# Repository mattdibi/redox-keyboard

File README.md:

<h3 align="center">The Redox project repository</h3>

<div align="center">

</div>

---

The Redox project is an open-source, [QMK (Quantum Mechanical Keyboard Firmware)](https://github.com/qmk/qmk_firmware) powered, ergonomic split mechanical keyboard. This repository will be used to share information about the project and instruction on how to use and assemble the Redox keyboard.

**Designer's bio**: [Mattia Dal Ben (aka u/TiaMaT102)](mailto:matthewdibi@gmail.com) obtained a master's degree in Electrical Engineering with a specialization in Computer Science at the University of Udine. Currently works as a Software Engineer in R&D department for a big IoT and Embedded Computers company. Mechanical keyboard enthusiast and maker, the Redox keyboard is the result of all of his passions.

## Rationale

The Redox is a keyboard project designed with ergonomics in mind. It uses Cherry MX style mechanical switches laid out in a 7x5 columnar stagger layout with components that can easily be sourced.

The design was heavily inspired by the [Ergodox keyboard](https://www.ergodox.io/), and its main goal is to reduce the size without sacrificing too many keys, hence the name **Re**duced Ergo**dox**.

As an Ergodox user I couldn't ignore the few flaws of the original design and in a moment of arrogance I tried to fix them, thus the Redox features:
- Easier to reach thumb cluster.
- Additional easy-to-reach rotated 1.25u thumb key.
- Reduced size.
- Reduced costs (the Redox uses Arduino Pro Micro instead of the Teensy 2.0).
- Either half can be plugged in to the PC since each half can act as the master.
- Either half can work as a standalone keyboard to be used as a macropad/gaming keyboard.
- RGB backlighting support.
- 3D-printer friendly case.
- Wireless [see section below](#wireless-implementations)
- [VIA](https://caniusevia.com/) compatible (thanks to [Harshit Goel](https://github.com/harshitgoel96))
- [ZMK firmware](https://zmk.dev/) compatible (thanks to [toddmok](https://github.com/toddmok))
- [KMK firmware](http://kmkfw.io/) compatible

## Related Projects

- [**Redox handwire**](https://www.thingiverse.com/thing:2704567): The first incarnation of the Redox keyboard. It consists of a 3D-printed case and a handwired matrix.
  - [Tilted Redox case](https://www.thingiverse.com/thing:2767216): tilted case for the Redox prototype by jschloer.
    - [Tilted redox case pro micro](https://www.printables.com/model/382413-tilted-redox-case-for-micro-and-usbc): Remix of the tilted case to support pro micro and usb c instead of TRRS. 

  - [couscous-kbd](https://gitlab.com/cschalkwijk/couscous-kbd): Redox-inspired parametric OpenSCAD keyboard design.
  - [Redox tenting kit](https://www.thingiverse.com/make:484843): modified base to support tenting, mini-USB for the interconnect, and a hole for microswitch for reset needed when uploading new firmware by [Lenbok](https://github.com/Lenbok).
  - [Iris-inspired Redox case](https://github.com/Lenbok/scad-redox-case): a case inspired both by the Redox rev1.0 and the Iris designed with OpenSCAD by [Lenbok](https://github.com/Lenbok).
  - [Redodactyl keyboard](https://www.reddit.com/r/MechanicalKeyboards/comments/9j5pw5/enter_the_redodactyl_first_build/): handwired 3D printed Dactyl-inspired Redox variant by u/darknao.
- [**Redox Manuform**](https://www.thingiverse.com/thing:3503380): full rework of the Redox case inspired by the Dactyl Manuform. Designed by [Fosk\_LL](https://www.thingiverse.com/Fosk_LL/about).
- [**Redox rev1.0**](https://github.com/mattdibi/redox-keyboard/tree/master/redox): the Redox rev 1.0 is the first commercially available version of the Redox keyboard.
	- Rev1.0 PCBs: available at [Falbatech's store](https://falbatech.click/products/REDOX-PCB-Electrical-Boards-Set-of-2-p613836203)
    - Firmware sources:
        - [QMK firmware for Redox](https://github.com/mattdibi/qmk_firmware/tree/master/keyboards/redox)
        - [KMK firmware for Redox](https://github.com/KMKfw/kmk_firmware/tree/master/boards/redox)
	- 3D-printable cases:
        - [3D printable case](https://www.thingiverse.com/thing:2886662), freely available.
        - [Redox keyboard case (high profile)](https://www.thingiverse.com/thing:3825752), by [Michele Ferri](https://www.thingiverse.com/sako83/about).
        - [Travel-friendly Redox Keyboard case](https://www.thingiverse.com/thing:3607303), by [Fosk\_LL](https://www.thingiverse.com/Fosk_LL/about).
        - [Redox Neodox case](https://github.com/Pastitas/Redox-neodox-Case), by [Pastitas](https://github.com/Pastitas)
        - [Redox big battery](https://github.com/marco-silvestri/redox-big-battery), by [Marco Silvestri](https://github.com/marco-silvestri).
	- Commercially available cases:
		- [Falbatech's bamboo cases with tilt kit](https://falbatech.click/products/REDOX-Standard-LIFT-Bamboo-Wood-Case-with-oil-finish-p613843480)
		- [Falbatech's fullhand bamboo cases](https://falbatech.click/products/search?keyword=redox%20fullhand%20bamboo)
- [**Redox rev1.0W**](https://github.com/mattdibi/redox-keyboard/tree/master/redox-w): the Redox rev 1.0W is the wireless version of the Redox keyboard.
    - Rev1.0W PCBs: gerbers available in [this repo](https://github.com/mattdibi/redox-keyboard/tree/master/redox-w/rev1.0W).
    - Falbatech's Rev1.0W Hot-swap PCBs: available at [Falbatech's store](https://falbatech.click/products/REDOX-Wireless-PCB-Electrical-Boards-Set-of-2-receiver-PCB-p613839986) (Incompatible with the 3D-printable cases down below)
    - Firmware sources:
        - [QMK firmware for Redox wireless](https://github.com/mattdibi/qmk_firmware/tree/master/keyboards/redox_w)
        - [Nordic MCUs firmware for Redox wireless](https://github.com/mattdibi/redox-w-firmware)
	- 3D-printable cases:
        - [3D printed case](https://github.com/mattdibi/redox-keyboard/tree/master/redox-w/case), freely available.
        - [Redox Neodox case](https://github.com/Pastitas/Redox-neodox-Case), by [Pastitas](https://github.com/Pastitas)
    - Commercially available cases (only compatible with the Falbatech's store PCBs):
        - [Falbatech's bamboo cases with tilt kit](https://falbatech.click/products/REDOX-Wireless-Standard-LIFT-Bamboo-Wood-Case-with-oil-finish-ver-1-p613842405)
		- [Falbatech's fullhand bamboo cases](https://falbatech.click/products/search?keyword=redox%20wireless%20bamboo%20fullhand)
- [**Redox rev2.0WHS**](https://github.com/mattdibi/redox-keyboard/tree/master/redox-w): the Redox rev 2.0WHS is the wireless hot-swappable version of the Redox keyboard.
    - Rev2.0WHS PCBs: gerber files available [here](https://github.com/mattdibi/redox-keyboard/tree/master/redox-w/rev2.0WHS/pcb)
    - Firmware sources:
        - [QMK firmware for Redox wireless](https://github.com/mattdibi/qmk_firmware/tree/master/keyboards/redox_w)
        - [Nordic MCUs firmware for Redox wireless](https://github.com/mattdibi/redox-w-firmware)
	- 3D-printable case:
        - [3D printed case](https://github.com/mattdibi/redox-keyboard/tree/master/redox-w/rev2.0WHS/case), freely available.

## Wireless Implementations

The Redox keyboard uses three different wireless implementations, differentiated by firmware:
 - *QMK based*: Leveraging the [Gazel protocol](https://developer.nordicsemi.com/nRF5_SDK/nRF51_SDK_v5.x.x/doc/5.2.0/html/a00140.html). It needs its own PCB and a receiver dongle (see [Redox Wireless](https://github.com/mattdibi/redox-keyboard/tree/master/redox-w) for details) and needs three YJ-14015 MCUs + a Pro Micro compatible controller.
 - *ZMK based*: Leveraging the Bluetooth protocol. It is based on the [Redox wired PCB](https://github.com/mattdibi/redox-keyboard/tree/master/redox) and the [nice!nano](https://nicekeyboards.com/nice-nano/) controller.
 - *KMK based*: Adding [Bluetooth Split](http://kmkfw.io/docs/split_keyboards#bluetooth-split-aka-no-trrs-currently-in-testing) code to `boards/redox/main.py`. Combined with a [compatible](http://kmkfw.io/docs/Officially_Supported_Microcontrollers) wireless controller completes wireless configuration. Would advice adding [Bluetooth keycodes](http://kmkfw.io/docs/keycodes#bluetooth-keys) in keymap; `keyboard.keymap` element in `main.py`.

 The notable differences for the three implementations are as follows:
 - _Battery life_: QMK Redox Wireless uses two CR2032 coin cell batteries which last [approximately one year (YMMV)](https://github.com/mattdibi/redox-keyboard/tree/master/redox-w#battery-usage), while the nice!nano support LiPo rechargable batteries (you can choose the capacity you want but expect them to last for a [few weeks on a single charge](https://zmk.dev/power-profiler)).
 - _Flexibility_: The receiver dongle limits the flexibility of QMK Redox Wireless.
 - _Cost_: The 3x YJ-14015 + Pro Micro combo is cheaper than two wireless controllers required for ZMK and wireless KMK.
 - _Range_: Bluetooth implementations, of ZMK and KMK, should be more capable than what can be achieved with the QMK Redox Wireless (At this point in time, I lack the evidence to support these claims though).

## Physical Key Layout

### Keycaps

| Size  | Qty |                                     Notes                                    |
|-------|:---:|:----------------------------------------------------------------------------:|
| 1.5u  |   6 |                                                                              |
| 1.25u |  10 | You can get away with 8 if you use two 1u keycaps for the 1.25u rotated keys |
| 1u    |  54 |                                                                              |

> :information_source: On [pimpmykeyboard.com](https://pimpmykeyboard.com/sa-1976-keyset-two-shot/) site you can find a SA 1976 keyset kit specifically made for the Redox keyboard: the "Ergo Redox kit (12 keys)".

## Affiliations

In partnership with Falbatech you can now use the code "**mattdibi05**" on Falbatech's store for a 5% OFF special discount.

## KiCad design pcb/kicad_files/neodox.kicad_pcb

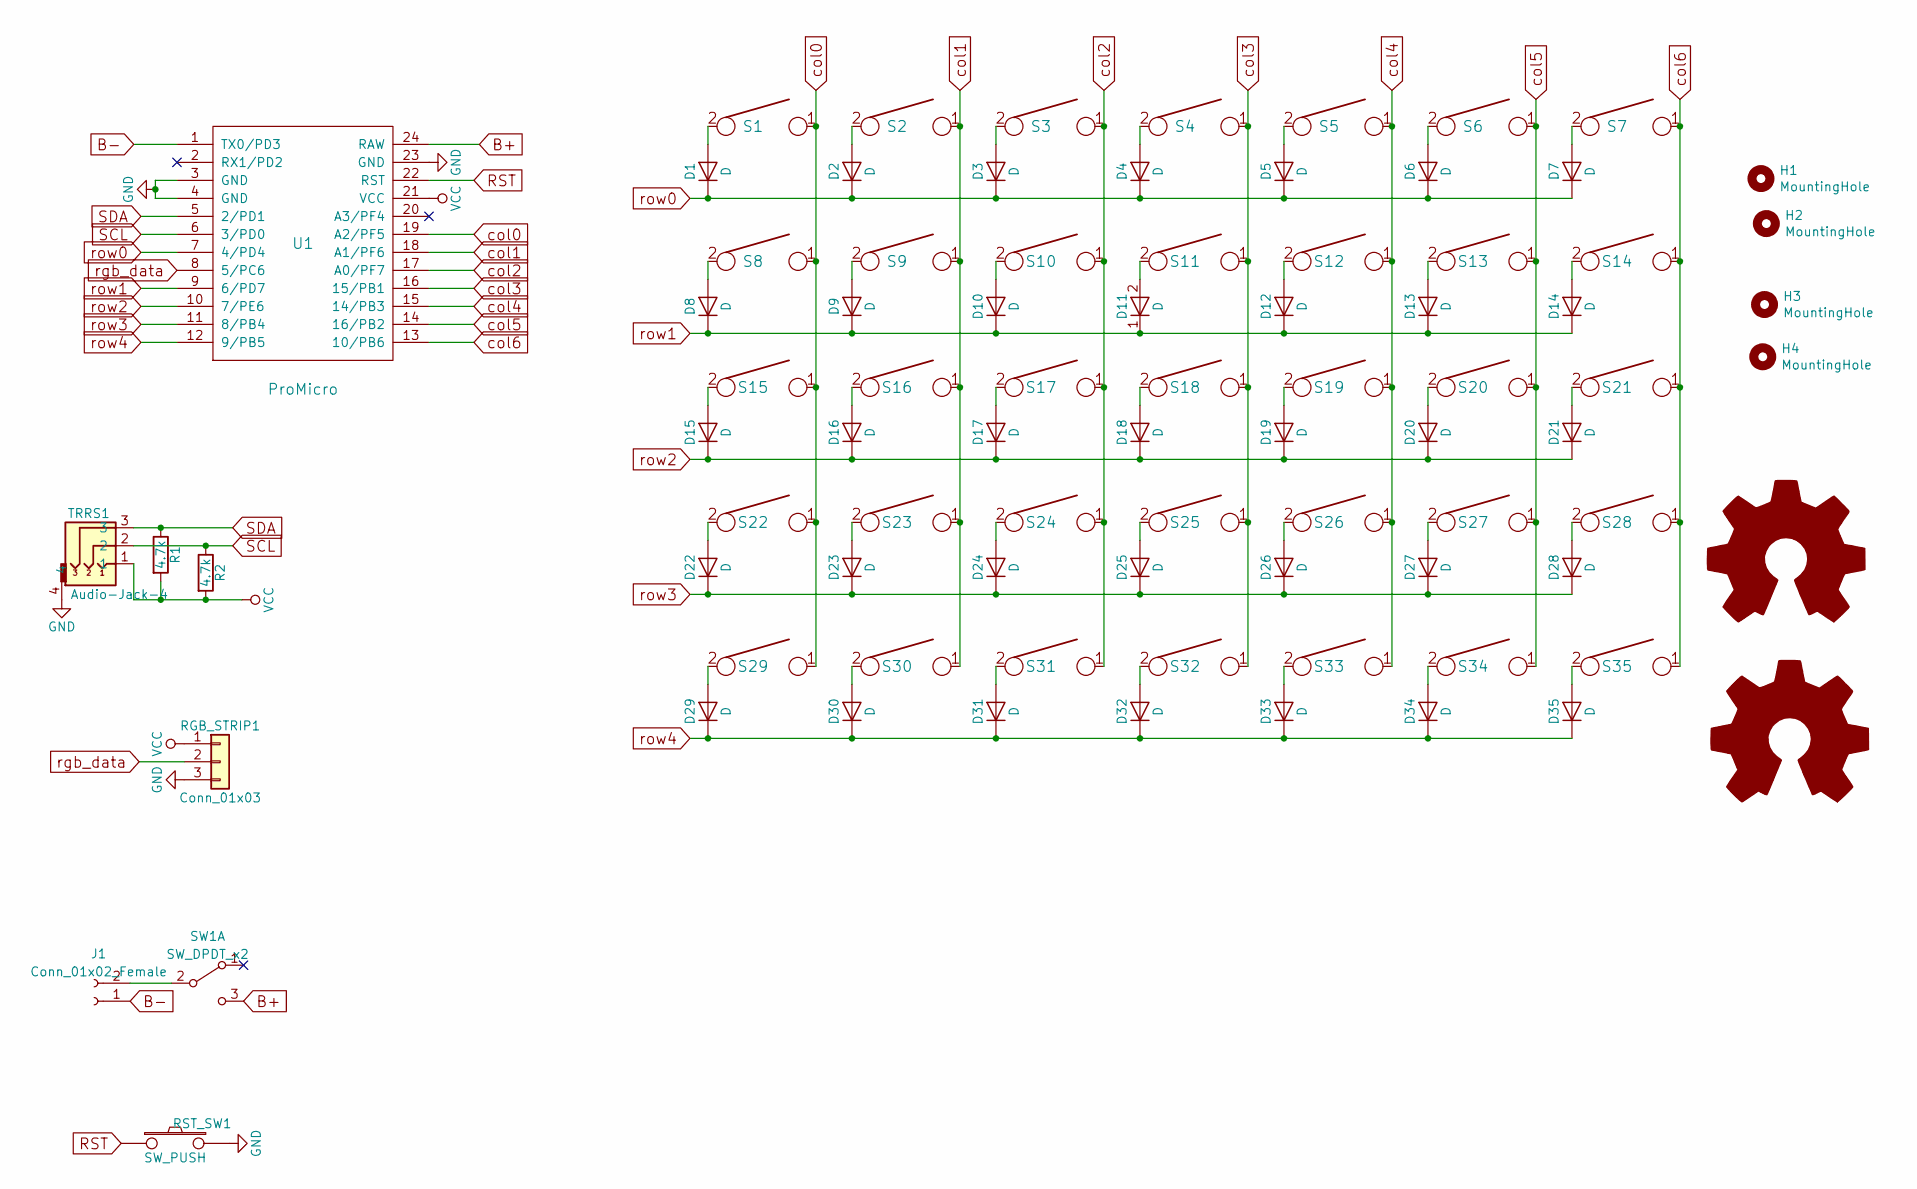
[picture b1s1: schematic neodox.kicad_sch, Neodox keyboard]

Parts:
D1, D2, D3, D4, D5, D6, D7, D8, D9, D10, D11, D12, D13, D14, D15, D16, D17, D18, D19, D20, D21, D22, D23, D24, D25, D26, D27, D28, D29, D30, D31, D32, D33, D34, D35: D; Diode-dual
H1, H2, H3, H4: MountingHole; MountingHole_3.2mm_M3
J1: Conn_01x02_Female; PinHeader_1x02_P1.27mm_Vertical
R1, R2: 4.7k; Resistor-Hybrid
RGB_STRIP1: Conn_01x03; PinHeader_1x03_P1.27mm_Vertical
RST_SW1: SW_PUSH; pushbutton_reversible
S1, S2, S3, S4, S5, S6, S7, S8, S9, S10, S11, S12, S13, S14, S15, S16, S17, S18, S19, S20, S21, S22, S23, S24, S25, S26, S27, S28, S29, S30, S31, S32, S33, S34, S35: KEYSW; Kailh_socket_MX_optional_reversible
SW1: SW_DPDT_x2; switch_reversible
TRRS1: Audio-Jack-4; PJ-320A
U1: ProMicro; ProMicro_unrouted

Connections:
B+: SW1.3 (C), U1.24 (RAW)
B-: J1.1, U1.1 (TX0/PD3)
GND: RGB_STRIP1.3, RST_SW1.2, TRRS1.4, U1.3 (GND), U1.4 (GND), U1.23 (GND)
unnamed: D1.2 (A), S1.2
unnamed: D2.2 (A), S2.2
unnamed: D3.2 (A), S3.2
unnamed: D4.2 (A), S4.2
unnamed: D5.2 (A), S5.2
unnamed: D6.2 (A), S6.2
unnamed: D7.2 (A), S7.2
unnamed: D8.2 (A), S8.2
unnamed: D9.2 (A), S9.2
unnamed: D10.2 (A), S10.2
unnamed: D11.2 (A), S11.2
unnamed: D12.2 (A), S12.2
unnamed: D13.2 (A), S13.2
unnamed: D14.2 (A), S14.2
unnamed: D15.2 (A), S15.2
unnamed: D16.2 (A), S16.2
unnamed: D17.2 (A), S17.2
unnamed: D18.2 (A), S18.2
unnamed: D19.2 (A), S19.2
unnamed: D20.2 (A), S20.2
unnamed: D21.2 (A), S21.2
unnamed: D22.2 (A), S22.2
unnamed: D23.2 (A), S23.2
unnamed: D24.2 (A), S24.2
unnamed: D25.2 (A), S25.2
unnamed: D26.2 (A), S26.2
unnamed: D27.2 (A), S27.2
unnamed: D28.2 (A), S28.2
unnamed: D29.2 (A), S29.2
unnamed: D30.2 (A), S30.2
unnamed: D31.2 (A), S31.2
unnamed: D32.2 (A), S32.2
unnamed: D33.2 (A), S33.2
unnamed: D34.2 (A), S34.2
unnamed: D35.2 (A), S35.2
unnamed: J1.2, SW1.2 (B)
RST: RST_SW1.1, U1.22 (RST)
SCL: R2.1, TRRS1.2, U1.6 (3/PD0)
SDA: R1.1, TRRS1.3, U1.5 (2/PD1)
VCC: R1.2, R2.2, RGB_STRIP1.1, TRRS1.1, U1.21 (VCC)
col0: S1.1, S8.1, S15.1, S22.1, S29.1, U1.19 (A2/PF5)
col1: S2.1, S9.1, S16.1, S23.1, S30.1, U1.18 (A1/PF6)
col2: S3.1, S10.1, S17.1, S24.1, S31.1, U1.17 (A0/PF7)
col3: S4.1, S11.1, S18.1, S25.1, S32.1, U1.16 (15/PB1)
col4: S5.1, S12.1, S19.1, S26.1, S33.1, U1.15 (14/PB3)
col5: S6.1, S13.1, S20.1, S27.1, S34.1, U1.14 (16/PB2)
col6: S7.1, S14.1, S21.1, S28.1, S35.1, U1.13 (10/PB6)
rgb_data: RGB_STRIP1.2, U1.8 (5/PC6)
row0: D1.1 (K), D2.1 (K), D3.1 (K), D4.1 (K), D5.1 (K), D6.1 (K), D7.1 (K), U1.7 (4/PD4)
row1: D8.1 (K), D9.1 (K), D10.1 (K), D11.1 (K), D12.1 (K), D13.1 (K), D14.1 (K), U1.9 (6/PD7)
row2: D15.1 (K), D16.1 (K), D17.1 (K), D18.1 (K), D19.1 (K), D20.1 (K), D21.1 (K), U1.10 (7/PE6)
row3: D22.1 (K), D23.1 (K), D24.1 (K), D25.1 (K), D26.1 (K), D27.1 (K), D28.1 (K), U1.11 (8/PB4)
row4: D29.1 (K), D30.1 (K), D31.1 (K), D32.1 (K), D33.1 (K), D34.1 (K), D35.1 (K), U1.12 (9/PB5)

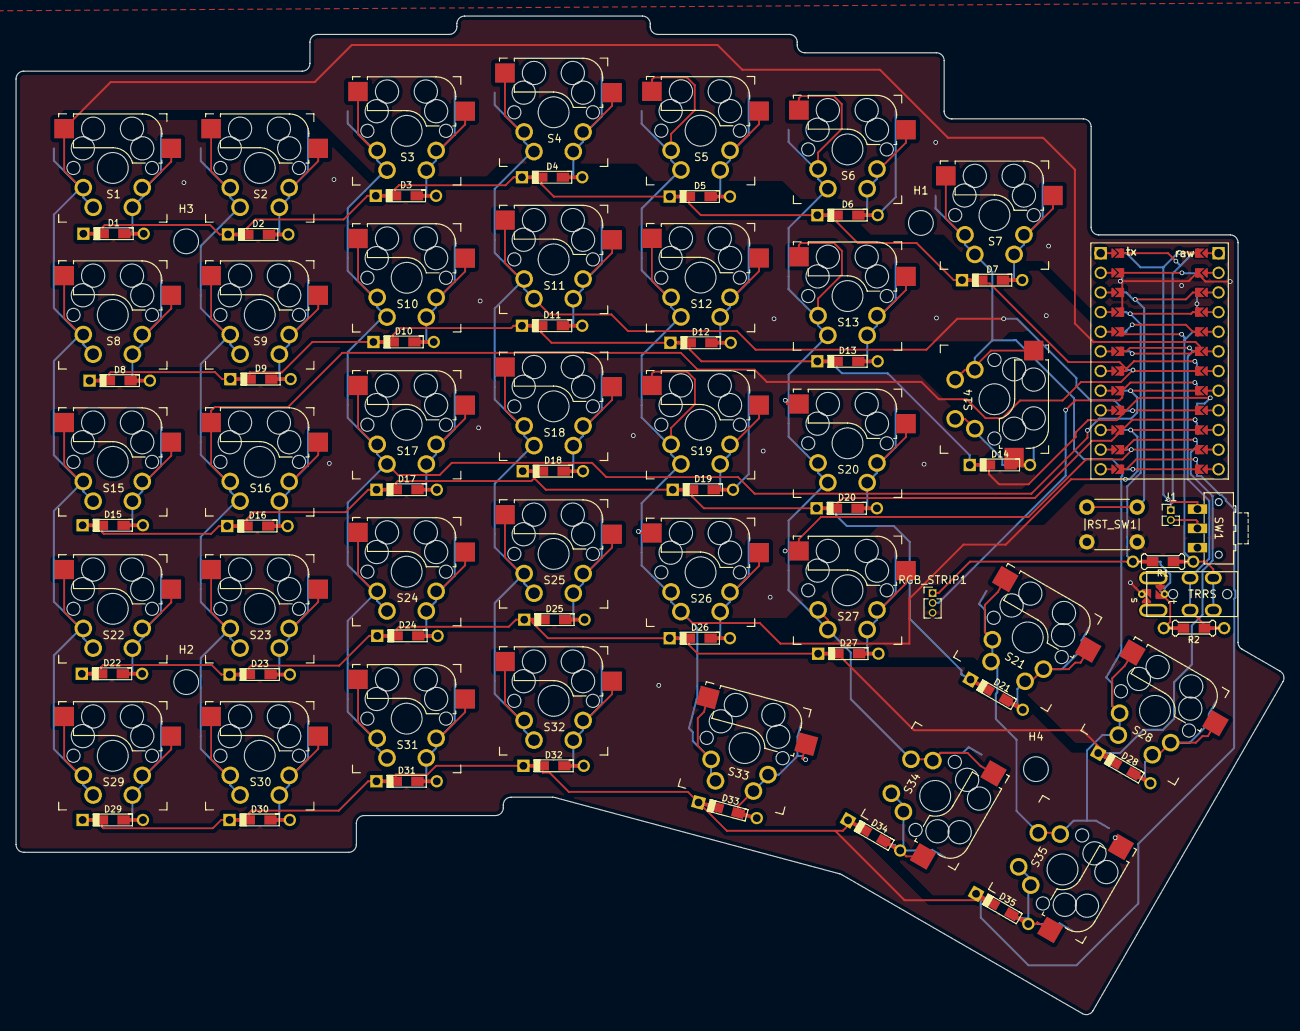
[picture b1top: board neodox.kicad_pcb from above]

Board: 2 copper layers, 163.9 x 129.1 mm, 82 parts (0 on the bottom side), 56 nets.

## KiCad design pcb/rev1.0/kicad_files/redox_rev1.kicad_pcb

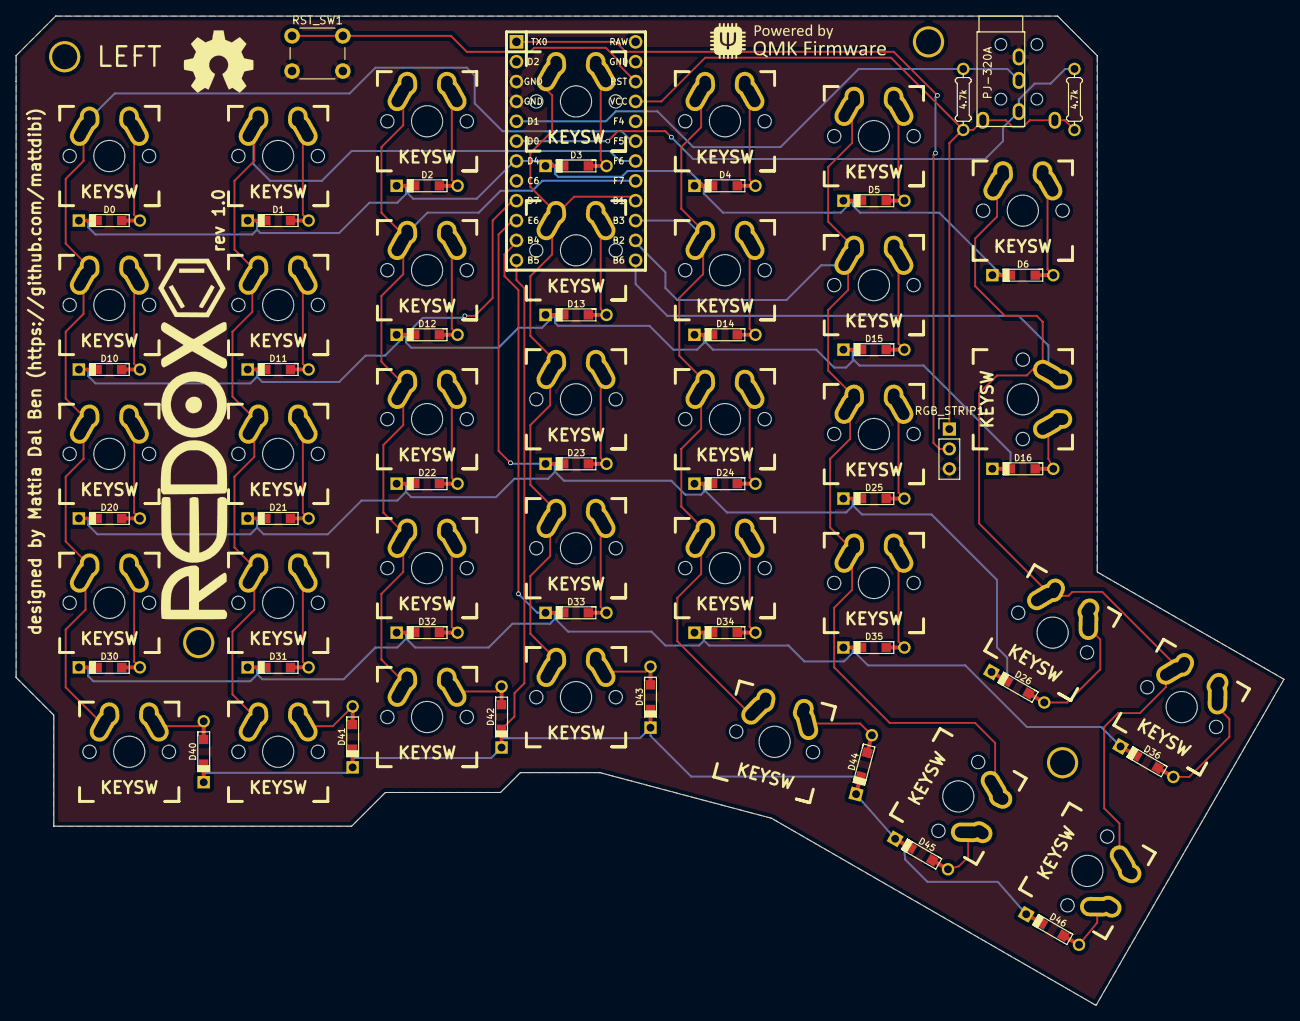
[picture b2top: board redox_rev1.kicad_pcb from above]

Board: 2 copper layers, 162.2 x 126.5 mm, 80 parts (0 on the bottom side), 53 nets.

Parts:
D0, D1, D2, D3, D4, D5, D6, D10, D11, D12, D13, D14, D15, D16, D20, D21, D22, D23, D24, D25, D26, D30, D31, D32, D33, D34, D35, D36, D40, D41, D42, D43, D44, D45, D46: D; Diode-dual
HOLE_M3, HOLE_M3#2, HOLE_M3#3, HOLE_M3#4: VAL**; HOLE_M3
K0, K10, K20, K30, K44: KEYSW; Mx_Alps_125-dualside
K1, K2, K3, K4, K5, K6, K11, K12, K13, K14, K15, K21, K22, K23, K24, K25, K26, K31, K32, K33, K34, K35, K36, K40, K41, K42, K43: KEYSW; Mx_Alps_100-dualside
K16, K45, K46: KEYSW; Mx_Alps_150-dualsided
R1, R2: 4.7k; Resistor-Compact
RGB_STRIP1: Conn_01x03; Pin_Header_Straight_1x03_Pitch2.54mm
RST_SW1: SW_PUSH; SW_PUSH_6mm_h4.3mm
TRRS1: Audio-Jack-4; TRRS-PJ-320A-dual
U1: ProMicro; ArduinoProMicro

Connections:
GND: RGB_STRIP1.3, RST_SW1.2, TRRS1.4, U1.3, U1.4, U1.23
unnamed: D0.2, K0.2
unnamed: D1.2, K1.2
unnamed: D2.2, K2.2
unnamed: D3.2, K3.2
unnamed: D4.2, K4.2
unnamed: D5.2, K5.2
unnamed: D6.2, K6.2
unnamed: D10.2, K10.2
unnamed: D11.2, K11.2
unnamed: D12.2, K12.2
unnamed: D13.2, K13.2
unnamed: D14.2, K14.2
unnamed: D15.2, K15.2
unnamed: D16.2, K16.2
unnamed: D20.2, K20.2
unnamed: D21.2, K21.2
unnamed: D22.2, K22.2
unnamed: D23.2, K23.2
unnamed: D24.2, K24.2
unnamed: D25.2, K25.2
unnamed: D26.2, K26.2
unnamed: D30.2, K30.2
unnamed: D31.2, K31.2
unnamed: D32.2, K32.2
unnamed: D33.2, K33.2
unnamed: D34.2, K34.2
unnamed: D35.2, K35.2
unnamed: D36.2, K36.2
unnamed: D40.2, K40.2
unnamed: D41.2, K41.2
unnamed: D42.2, K42.2
unnamed: D43.2, K43.2
unnamed: D44.2, K44.2
unnamed: D45.2, K45.2
unnamed: D46.2, K46.2
RST: RST_SW1.1, U1.22
SCL: R2.1, TRRS1.2, U1.6
SDA: R1.1, TRRS1.3, U1.5
VCC: R1.2, R2.2, RGB_STRIP1.1, TRRS1.1, U1.21
col0: K0.1, K10.1, K20.1, K30.1, K40.1, U1.19
col1: K1.1, K11.1, K21.1, K31.1, K41.1, U1.18
col2: K2.1, K12.1, K22.1, K32.1, K42.1, U1.17
col3: K3.1, K13.1, K23.1, K33.1, K43.1, U1.16
col4: K4.1, K14.1, K24.1, K34.1, K44.1, U1.15
col5: K5.1, K15.1, K25.1, K35.1, K45.1, U1.14
col6: K6.1, K16.1, K26.1, K36.1, K46.1, U1.13
rgb_data: RGB_STRIP1.2, U1.1
row0: D0.1, D1.1, D2.1, D3.1, D4.1, D5.1, D6.1, U1.7
row1: D10.1, D11.1, D12.1, D13.1, D14.1, D15.1, D16.1, U1.9
row2: D20.1, D21.1, D22.1, D23.1, D24.1, D25.1, D26.1, U1.10
row3: D30.1, D31.1, D32.1, D33.1, D34.1, D35.1, D36.1, U1.11
row4: D40.1, D41.1, D42.1, D43.1, D44.1, D45.1, D46.1, U1.12

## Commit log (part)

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2018-03-24 Added assembly instructions
2018-03-24 Swtiched to table for BoM
2018-03-24 Added designer bio and related projects
2018-03-24 Improved english
2018-03-31 Added RGB underglow instructions
2018-03-31 Some small corrections.
2018-03-31 Fixed links
2018-03-31 Fixed lists
2018-04-29 Added rgb-backlight firmware instructions
2018-04-29 Added labels inside RGTB underglow pictures
2018-04-29 Added QMK references
2018-04-30 Added 3D printable case files
2018-04-30 Removed license
2018-04-30 Added LICENSE file
2018-04-30 Changed to MIT license
2018-04-30 Renamed files
2018-05-05 Added 1uLayout image
2018-05-05 Added new layout references
2018-05-05 Forgot to move KLE layout permalink
2018-05-05 Added schematic
2018-05-05 Added switch location image
2018-05-06 Added EE_hands guide
2018-05-12 Fixed broken link
2018-05-13 Added some more informations and links
2018-05-13 Added pre-built hex files for testing
2018-05-19 Added .dxf and .svg files
    Added .dxf and .svg files to make it easier for people to create their own cases.
2018-05-19 Updated layout with default mappings
2018-05-19 Improved layout images
2018-06-03 Added Falbatech's case instructions
2018-06-05 Added Lenbok's Iris-inspired Redox case
2018-06-09 Added rationale
2018-06-10 Corrected typo
2018-07-09 Added ProMicro installation details
2018-08-21 Updated available cases.
2018-08-23 Added PCB files
2018-08-23 Added reference to project Ultron
2018-08-25 Added build log
2018-09-16 Updated build logs
2018-09-16 Added RGB underglow firmware note
2018-09-16 Added styling to RGB underflow note
2018-09-22 Moved redox instruction to redox/ folder
2018-09-22 Added redox-w/ folder
2018-09-22 Minor changes to READMEs
2018-09-22 Added firmware instructions
2018-09-22 Fixed typo
2018-09-22 Fixed broken links
2018-09-22 Added 3D printable plate files
2018-09-23 Added project log link
2018-09-29 Added Wireless Redox assembly instructions
2018-09-29 Added assembly images
2018-09-29 Updated build log
2018-09-29 Added ST-Link v2 image and references
2018-09-29 Reduced image size
2018-09-29 Added reference to picture
2018-09-29 Removed link
2018-09-29 Added bettery installation detail
2018-09-29 Better pic
2018-09-29 Updated main README
2018-10-07 Added precompiled firmware files
2018-10-14 Added receiver assembly instructions
2018-10-14 Fixed broken images links
2018-10-20 Added gerber files
2018-10-20 Added KiCad project files
2018-10-20 Updated precompiled QMK hex
2018-11-10 Improved bottom case for Wireless Redox rev.1.0
2018-11-10 Improved case for Redox rev.1.0
2018-11-11 Updated project build logs links
2018-11-17 Added 3D printed case materials detail
2018-11-24 Removed obsolete note
2018-11-24 Moved the external links section up
2018-12-25 Added redox-w receiver files.
2018-12-25 Removed old instructions
2018-12-25 Improved BOM. Added `Resistor values` `Default configuration` sections
2018-12-25 Added receiver PCB images
2018-12-25 Image resize.
2018-12-29 Fixed wrong compilation instruction
2018-12-29 Improved firmware instructions
2018-12-29 Added Redox-W firmware diagram sources
2018-12-30 Added battery usage section
2019-01-02 Added Receiver assembly images
2019-01-02 Added notes
2019-01-02 Redox receiver (#12)
    * Added redox-w receiver files.
    * Updated receiver BOM
    * Removed old instructions
    * Improved BOM. Added `Resistor values` `Default configuration` sections
    * Added receiver PCB images
    * Image resize.
2019-01-02 Improved instruction readability
2019-01-02 Moved note at start of subsection
2019-01-02 Removed repeated section
2019-01-02 Added some more references
2019-02-16 Added first draft of the instructions
2019-02-16 Added some more screenshots
2019-02-16 Added ST-Link debugger wiring pic
2019-02-18 Added Redox rev. 1 hot swap mod instructions
2019-02-18 Hot swap mod typo fixes
2019-02-18 Corrected hot swap mod finished image
2019-02-18 Document the Mill-Max and Peel-A-Way hotswap mod (#17)
    * Added Redox rev. 1 hot swap mod instructions
    * Hot swap mod typo fixes
    * Corrected hot swap mod finished image
2019-03-03 Added OSHW logo
2019-03-23 Updated EE_hands instructions
2019-03-23 Added link to Redox-w firmware sources
2019-03-23 Added Redox Manuform reference
2019-04-13 DOCS: Added update before install of openocd
2019-05-04 Added note for Green Pro Micros problem
2019-05-04 Added note no Green Pro Micro color
2019-05-04 Improved video link styling
2019-05-05 Added link to Travel-friendly Redox Keyboard case by Fosk_LL
2019-05-05 Added links to new Falbatech's Redox wireless cases
2019-07-01 DOCS: Added brief explaination of the inner workings of the keyboard
2019-07-01 DOCS: Added link to Mitosis repo
2019-08-04 Updated Redox-Wireless precompiled hexes to new version
2019-08-19 fix for the default layout
    Added /? to the default position for a qwerty keyboard. Moved |\ to the left ctrl with the same behaviour as before.
2019-08-19 DOCS: Updated with new default layout
2019-08-25 Added Redox keyboard case (high profile) by Michele Ferri link
2019-10-23 Fix a few typos I noticed.
2020-02-02 DOCS: Updated with improved firmware instructions
2020-05-29 Added badges
2020-05-29 Moved title
2020-05-29 Feature/doc improvements (#61)
    * Added badges
    * Moved title
2020-06-10 feat: Added STL for switch (#62)
    Switch slots into hole in the front of case. It has a slot for the switch specified in the BOM and a pincer for a top mount switch.
2020-06-19 IO switched to correct way around
    Had them backward in first commit
2020-06-19 Reciever made bigger to fit
2020-06-20 Added wireless case CAD files
2020-06-20 Feature: CAD files (#64)
    * Added wireless case CAD files
    * Added wired CAD files
2020-06-23 Feat: Added a 3d printable stand
    Angles are 8 degrees of tilt and 8 degrees of roll. Comfy for me, but could add others.
2020-06-29 Improved STL and removed keymaps
    Added nice snap fittings to the receiver case and made the angle stand a lot cleaner, and sections to put non-slip feet on
2020-10-25 Added new video guide link
2020-10-25 Resized video thumbnail
2020-10-25 Docs update (#75)
    * Added new video guide link
    * Resized video thumbnail
2020-11-07 add a CAD file for tray-mounted plate
2021-01-02 Added note about VIA compatibility
2021-01-02 Updated shameless donate button
2021-01-02 Added KLE layout image
2021-01-02 Added pimpmykeyboard Redox keyset link
2021-01-02 Docs update (#79)
    * Added note about VIA compatibility
    * Updated shameless donate button
    * Added KLE layout image
    * Added keycaps section
    * Added pimpmykeyboard Redox keyset link
2021-02-20 Added Redox Neodox case links
2021-02-20 Refactored README links
2021-02-20 Changed titles for consistency
2021-02-20 Added brief description of the keyboards
2021-02-20 Removed redundant description
2021-04-04 Moved rev1.0W files in relative folder
2021-04-04 Added rev2.0WHS PCB files in new folder
2021-04-04 Added rev2.0WHS case files
2021-04-04 Added docs
2021-04-04 Updated summary
2021-04-04 Added 3D printed case notes
2021-04-04 Added 3d printed case image
2021-04-04 Added transmitter installation instructions
2021-04-04 Added some more images
2021-04-04 Improved assembly instructions
2021-04-04 Added 2.0WHS references to landing page
2021-04-04 Added receiver schematic and gerbers
2021-04-04 Added case compatibility note
2021-04-04 Added transmitters schematic
2021-04-04 Added case compat image
2021-04-04 Added link to case compatibility section
2021-04-04 Feature: Redox rev.2.0WHS (#99)
    * Moved rev1.0W files in relative folder
    * Added rev2.0WHS PCB files in new folder
    * Added rev2.0WHS case files
    * Added docs
    * Fixed broken image urls
    * Fixed broken image urls
2021-04-05 Updated precompiled binaries
2021-04-05 Added note about battery usage
2021-04-05 Removed unnecessary columns
2021-04-05 Added link to case
2021-04-05 Added details about Pro Micro installation
2021-04-05 Added link
2021-04-05 Refactoring: Docs (#100)
    * Merged READMEs into a single one
    * Added note about battery usage
    * Removed unnecessary columns
    * Added link to case
    * Added details about Pro Micro installation
    * Fixed URL
2021-04-05 Added PCB manufacturing links
2021-04-06 Added missing change in units
2021-04-06 DOCS: Fix typo in current consumption formula for redox-w (#102)
    * DOCS: Fix typo in current consumption formula for redox-w
    * Added missing change in units
2021-04-06 Added instructions for fw upload using Docker containers
2021-04-06 Removed unnecessary images
2021-04-06 Added docker-compose stop output
2021-04-06 Feature: Docker FW upload instructions (#103)
    * Added instructions for fw upload using Docker containers
    * Removed unnecessary images
    * Added udev rules and repo download instructions
    * Added docker-compose stop output
2021-04-30 Add another detailed build guide
    Hey, I love redox. I have written a guide/journal entry about my build. I will as well have a video soon.
    Here is a pull request with a link to that journal entry, if you'd like to add it to the readme.
2021-11-14 Update README.md
    Added warning to make sure that promicros is alright before start. Seriously, guys unsoldering them afterwards is painfull 😞
2021-11-15 Update README.md (#120)
    Added warning to make sure that promicros is alright before start. Seriously, guys unsoldering them afterwards is painfull 😞
2021-11-15 Formatting fix
2022-01-16 Added info about ZMK wireless implementation
2022-01-16 Added redox wireless implementations comparison
2022-01-16 Moved wireless implementations details into their own section
2022-01-16 Fixed issues in markdown syntax
2022-01-16 Docs: ZMK update (#127)
    * Added info about ZMK wireless implementation
    * Fixed typo in url
    * Added redox wireless implementations comparison
    * Moved wireless implementations details into their own section
    * Fixed issues in markdown syntax
    * Fixed battery life section
2022-02-18 removed dead links, updated infos on the falba cases
2022-02-19 Added note about compatible cases
2022-02-19 removed dead links, updated infos on the falba cases (#129)
    * removed dead links, updated infos on the falba cases
    * Added note about compatible cases
2022-03-25 Updated 3D printable cases (#135)
2022-08-16 Recreate the KiCad files for the redox-w rev2WHS
    Archive the project to make it portable instead of zipping the files
    add via to ground island
2022-09-28 Add link to wooden case build
2023-01-27 add handmade wood case project link
2023-01-28 Added remixed version of tilted case
2023-02-03 Added remixed version of tilted case (#161)
2023-02-10 remix files for footprints and placement
2023-02-10 add gitignore
2023-02-10 add cutout
2023-02-13 add all features and board layout, pending routing
2023-04-12 move config
2023-04-12 layer 1 ready
2023-04-12 layer 1 full
2023-04-12 base and gamin layers ready
2023-04-12 layer 2 done
2023-04-12 Move agasin
2023-04-14 move tha stafff
2023-04-17 Added different ble setup
2023-05-13 Update README.md (#169)
2023-05-31 Rename Neodox_README.md to README.md
2023-08-05 Build and pcb changes
2023-08-05 Change controls for bluetooth and layer change
2023-08-05 Add the docker setup (not currently working)
2024-01-07 fix dead link
2024-01-07 fix dead link (#177)
2024-01-11 rename kikad project files
2024-01-11 Modified buildmd and gitignore
2024-01-11 modified keyboard name
2024-01-11 change build docs and filenames
2024-01-11 change build
2024-01-11 Added final lines to build script and new firmwares
2024-05-04 fix broken link
2024-05-05 fix broken falbatech links (#178)
    * fix broken link
    * fix broken link
    * fix broken links
    * fix broken link
    * fix broken link
2026-05-19 Update copyright year and name in LICENSE file
    It's been 8 years and I noticed only now -..-

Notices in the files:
README.md:
License: MIT
